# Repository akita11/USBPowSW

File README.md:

# USBPowSW

## これは何？

PCとUSB機器の間のUSB-Aコネクタ(平コネクタ)に接続し、USB機器の電源のON/OFFを行うデバイスです。
マイコン(ATtiny10)が載っていて、ON/OFF制御をプログラムできます。

## 使い方

PCとUSB機器の間の、USB-Aコネクタ(平コネクタ)に接続します。
初期設定ではタクトスイッチを押すごとにON/OFFが切り替わります。（電源ON時にはLEDが点灯します。）

## もっと使い込むには・・・

[回路図](https://github.com/akita11/USBPowSW/blob/main/USBPowSW_schematic.png)と
[プログラム](https://github.com/akita11/USBPowSW/blob/main/USBPowSW.ino)を参考に、
電源ON/OFFを制御するプログラムを書くことができます。
ボード上のタクトスイッチの他、汎用のIOピンを接続する端子をつけることで、そのIOピンの情報も使って制御することができます。

- PB0 : 外部端子に接続（初期状態は未接続）
- PB1 : ボード上のタクトスイッチ（押すと0)
- PB2 : USB電源制御(0=ON、1=OFF）

ATtiny10のプログラム開発や書き込みをArduinoIDEから行う方法は、[kosakalab](https://make.kosakalab.com/make/electronic-work/arduino-ide/arduino_tpi/)などを参考にしてください。(ArduinoIDE1.8.9が必要です)
また書き込みは、この方法や、Atmelマイコンの書き込み機(AVR-ISP mkIIなど)を使用してください。
（通常のArduinoのように、PCと接続して直接の書き込みはできません）

## Author

Junichi Akita (akita@ifdl.jp, @akita11)

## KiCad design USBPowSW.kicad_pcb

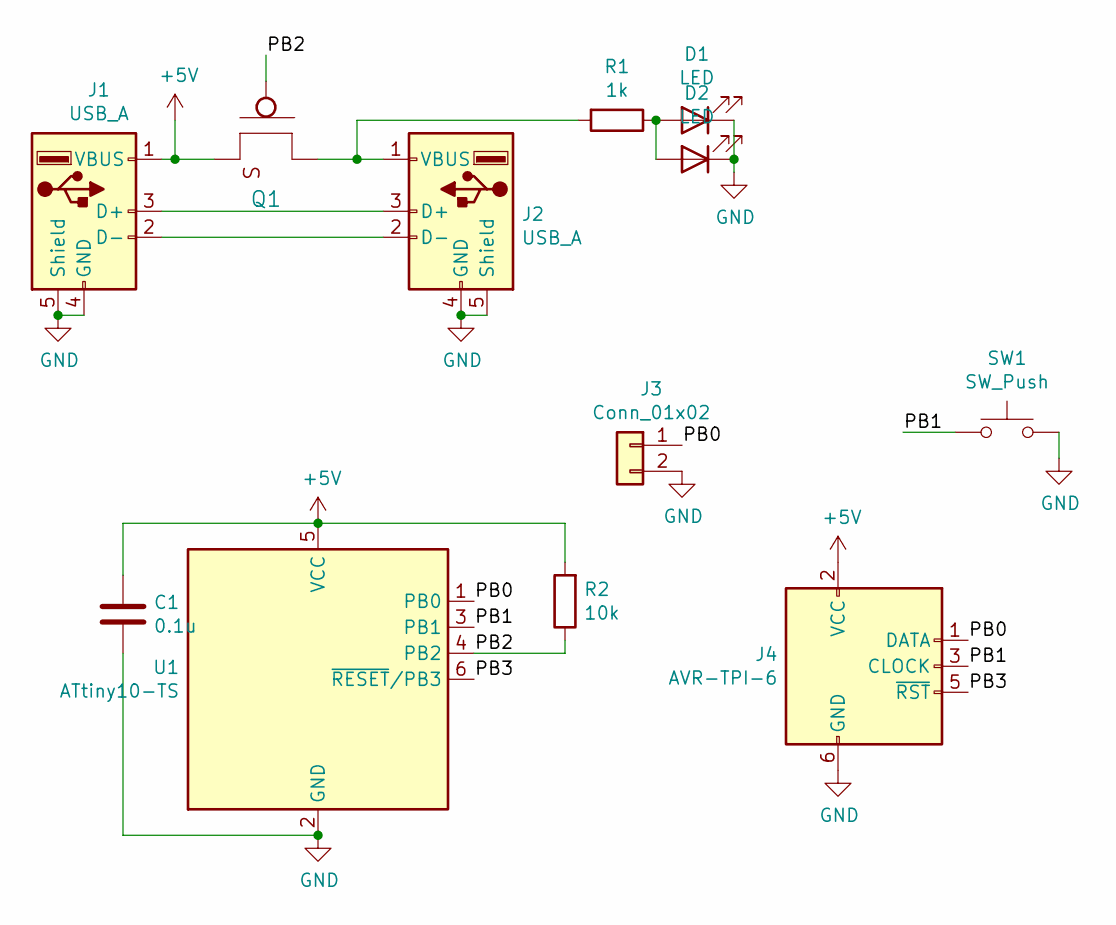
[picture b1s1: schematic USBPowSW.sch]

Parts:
C1: 0.1u; C_0603_1608Metric
D1: LED; LED_0603_1608Metric
D2: LED; LED_D5.0mm_Clear
J1: USB_A; USB-A_plug
J2: USB_A; USB_A_Molex_67643_Horizontal
J3: Conn_01x02; PinSocket_1x02_P2.54mm_Vertical
J4: AVR-TPI-6; PinHeader_2x03_P2.54mm_Vertical
Q1: TR_PMOS_IRLML6402; SOT-23
R1: 1k; R_0603_1608Metric
R2: 10k; R_0603_1608Metric
SW1: SW_Push; SW_PUSH_6mm
U1: ATtiny10-TS; SOT-23-6

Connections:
+5V: C1.1, J1.1 (VBUS), J4.2 (VCC), Q1.2 (S), R2.2, U1.5 (VCC)
/PB0: J3.1, J4.1 (DATA), U1.1 (PB0)
/PB1: J4.3 (CLOCK), SW1.1, U1.3 (PB1)
/PB2: Q1.1 (G), R2.1, U1.4 (PB2)
/PB3: J4.5 (~RST), U1.6 (~RESET~/PB3)
GND: C1.2, D1.1 (K), D2.1 (K), J1.4 (GND), J1.5 (Shield), J2.4 (GND), J2.5 (Shield), J3.2, J4.6 (GND), SW1.2, U1.2 (GND)
unnamed: D1.2 (A), D2.2 (A), R1.1
unnamed: J1.2 (D-), J2.2 (D-)
unnamed: J1.3 (D+), J2.3 (D+)
unnamed: J2.1 (VBUS), Q1.3 (D), R1.2

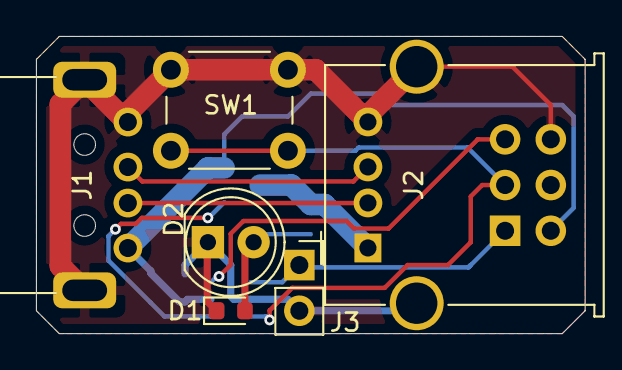
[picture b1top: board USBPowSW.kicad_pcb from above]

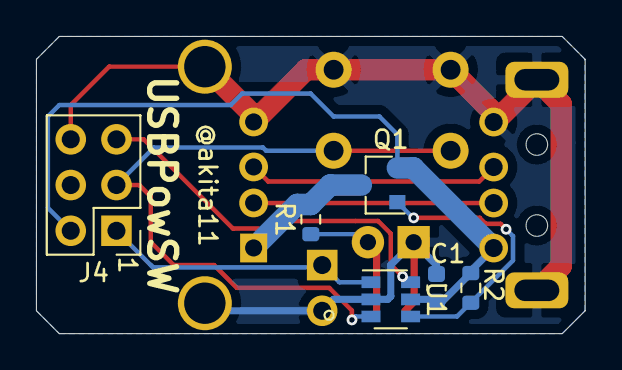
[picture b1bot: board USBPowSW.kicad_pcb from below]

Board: 2 copper layers, 30.5 x 16.5 mm, 12 parts (6 on the bottom side), 10 nets.

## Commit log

2021-05-27 ソースコードの追加
